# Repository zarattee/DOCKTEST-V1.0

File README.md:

# DOCKTEST-V1.0
 DOCK TEST para conector tipo v8

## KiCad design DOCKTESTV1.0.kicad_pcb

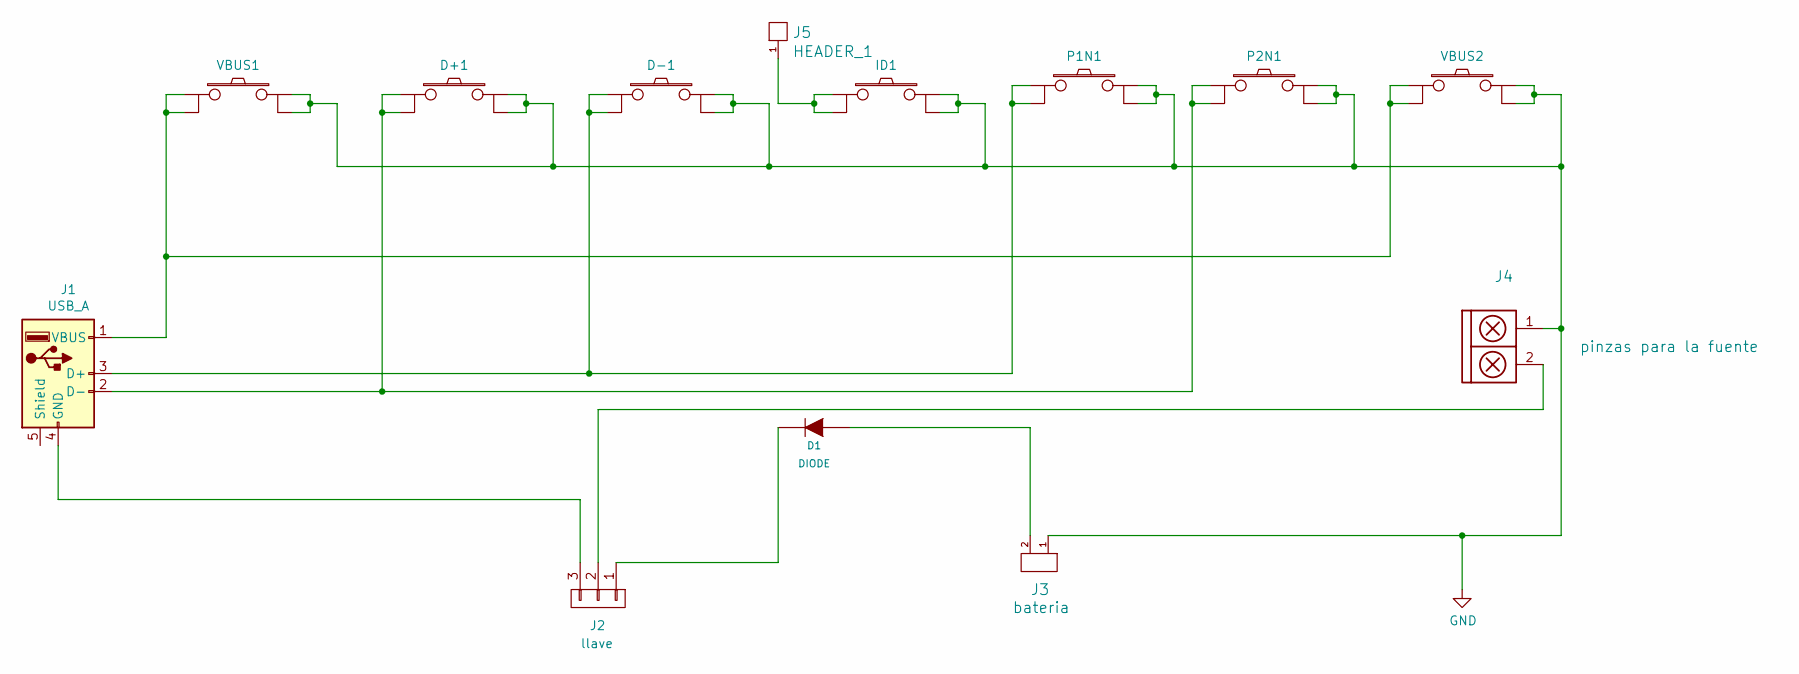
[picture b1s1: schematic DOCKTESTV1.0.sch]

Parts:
D1: DIODE; DO-41
D+1: SW_PUSH; Pulsador_TH_4
D-1: SW_PUSH; Pulsador_TH_4
ID1: SW_PUSH; Pulsador_TH_4
J1: USB_A; USB_A_Stewart_SS-52100-001_Horizontal
J2: llave; Pin_Strip_3
J3: bateria; BatteryHolder_Keystone_500
J4: pinzas para la fuente; BORNERA2_DUO
J5: HEADER_1; Cable_1,5mm
P1N1, P2N1: SW_PUSH; Pulsador_TH_4
VBUS1, VBUS2: SW_PUSH; Pulsador_TH_4

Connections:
GND: D+1.3, D+1.4, D-1.3, D-1.4, ID1.3, ID1.4, J3.1, J4.1, P1N1.3, P1N1.4, P2N1.3, P2N1.4, VBUS1.3, VBUS1.4, VBUS2.3, VBUS2.4
unnamed: D1.1 (A), J3.2
unnamed: D1.2 (K), J2.1
unnamed: D+1.1, D+1.2, J1.2 (D-), P2N1.1, P2N1.2
unnamed: D-1.1, D-1.2, J1.3 (D+), P1N1.1, P1N1.2
unnamed: ID1.1, ID1.2, J5.1
unnamed: J1.1 (VBUS), VBUS1.1, VBUS1.2, VBUS2.1, VBUS2.2
unnamed: J1.4 (GND), J2.3
unnamed: J2.2, J4.2

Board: 2 copper layers, 13 parts (0 on the bottom side), 9 nets, no tracks yet.

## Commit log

2021-07-06 commit inicial
2021-07-06 h
    h
2021-07-07 modificacion en el sch,pcb
    se modifico una linea de gnd en el pcb y tambien se empezo el ruteo del pcb
